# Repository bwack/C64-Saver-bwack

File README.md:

C64 Saver v1 and v2
- Overvoltage protection for the C64 and its power brick.

Designed by BWACK 2018
CERN OPEN HARDWARE LICENSE v1.2
http://www.ohwr.org/

The KiCad and other design files are available on GitHub:
https://github.com/bwack/

All text above must be included in any redistribution

# Warning: latest version of the savers are not tested.

# Bwack's C64 saver designs.

The C64 Saver 2 is an open-source project intended to make overvoltage protection available and easy to make for anyone interested in using the old Commodore power brick together with the C64. The power brick is 30-40 years old, and it is known for failure with overvoltage. This is caused sometimes because of broken solder joints on the regulator or the regulator itself failing.

## What has changed in v2 ?
- The design is modular.
- Spike protection. Handles hotswapping and switch bouncing better.
- It is much much easier and faster to make. Most people can make it!

## The base board (C64 Saver 2 SMD or Throughhole)
The base board is all you need for overvoltage protection. Through hole parts except for the mosfet, but it is large and easy to solder, no special tools needed other than your solder iron. The board shape fits the Hammond 1551g project case.
* Note: You need to bridge pin 4 and 5 in J2 and pin 4 and 5 in J4 if you are not using the base board in combination with the addon board or the relay board. The reason for this is that, with the addon board, we need to route the current through a sensing circuit. When the addon board is not used, we need to route it directly to the mosfet and terminals.

There is also a SMD version for those who like to reflow soldering.

## The addon board
The C64 saver addon board is a hat for the base board, and adds software control, instrumentation on both ac and dc side, and an optional 128x32 OLED display. The aim for this project is to make a tool for C64 repairers. The 9VAC and 5VDC are fully isolated. Software control and instrumentation is useful if you are repairing C64s. You can set the output to shut down in case of an overcurrent condition. If an overvoltage happens you can configure the saver to auto reset or keep the power from comming back on again. There are several reasons why you might want this. C64 PSUs that need service, the capacitors are dry and the 5VDC has an AC component on it. The saver would normally just go on and off at 100Hz. The software control can detect this. The other problem is if the computer has a faulty chip that cause massive current draw on the 5V. The fuse might not blow because it is not enough, then you can configure the saver cut if you desire. I'm not gonna lie. This is my pet project, and the cost has not been a topic on my mind.

The C64 Saver Addon Board 1.4:

Youtube video of me testing the addon board installed on the C64 Saver 2.

The relay and hold board is archived in the oldfiles folder.

## C64 Saver OCP

OCP, not robocop, but overcurrent protection. Is a new circuit that I'm working on. It has three LEDs and a button. The overvoltage protection circuit is the same as before. The overcurrent will light the yellow led and keep it lit and keep the output OFF after an overcurrent event.

## The old design
I have decided to release my older C64 Saver v1. The board that fits inside a connector. Time and skill is super high on this product so be warned ! (SMD 0603, solder blob connections, tight spaces and short circuit hazards).

## Gerbers
If you are looking for gerbers, click the releases tab. There you will find a zip file of gerber for each release.

# BOM
All bill of materials (BOM) are moved into the respective project folders. I have added digikey etc order no. in the parts in the schematics such that they will show up in the interactive boms.

Here are the interactive BOMs:

[ibom for C64 Saver Throughole 2.6](https://htmlpreview.github.io/?https://github.com/bwack/C64-Saver-bwack/blob/master/C64%20Saver%20Throughhole%202.6/bom/ibom.html)

[ibom for C64 Saver SMD 2.6](https://htmlpreview.github.io/?https://github.com/bwack/C64-Saver-bwack/blob/master/C64%20Saver%20SMD%202.6/bom/ibom.html)

[ibom for C64 Addon Board 1.4](https://htmlpreview.github.io/?https://github.com/bwack/C64-Saver-bwack/blob/master/addon%20board%201.4/bom/ibom.html)

[ibom for C64 Saver OCP 0.1](https://htmlpreview.github.io/?https://github.com/bwack/C64-Saver-bwack/blob/master/C64%20Saver%20OCP%200.1/bom/ibom.html)

# Changelog:

- C64 Saver 2.6 (THT+SMD) and Addon Board 1.4 (2023-04-02)
  - Replaced 7n2002 with BC547/BC847 to fix the tolerance issues.
  - Throughhole and SMD: same version numbers, same circuits, same reference numbers.
  - Red LED is switched by TL431 and Green by BC547/BC847.
  - Added LEDs to the Throughhole version. It was a challenge.
  - Fix: The Addon Board 1.3 had incorrect pinout for the 5V reg.
  - I never tested the Addon Board 1.3, but thanks to Retroisten who sent.
  me images and advicing me about he pinout, I'm very happy about it. He also
  showed me that it does work, with the regulator hacked in.  In this version 1.4
  it is working.

- C64 Saver 2.5 (SMD) (2020-09-13)
  - Added fault LED and power LED
  - 0805 SMD resistors
  - SOT23-5 TL431 and NMOS

- RelayHold 0.2 (2019-08-25)
  - Initial release
  - All through-hole parts.

- Addon Board 1.3 (2019-05-24)
  - Changed optocoupler footprint to more common SOIC-4_4.55x2.6mm_P1.27mm
  - Larger 5V regulator on 9vac side for less heat
  - replaced 100uF tantalum with 3x 47uF 1206 MLCC
  - kicad 5.1.0 project

- Addon Board 1.2 (2018-11-11)
  - Swapped HOLD_ with SENSE_VAC on the MCU. SENSE_VAC needs ADC.
  - Correct the mixed up SDA and SCL.
  - 5V supply to the 5V section is moved to VIN+ (before the shunt).
    To not pull power through the sensing resistor.
  - 4k7 I2C pullups.https://htmlpreview.github.io/?https://github.com/bwack/C64-Saver-bwack/blob/develop/C64%20Saver%20Throughhole%202.6/bom/ibom.html

- C64 Saver 2.4 (2018-09-23)
  - Support lower Vth on Q1. Resistor divider R7 and R8.
  - Remove C2 to make room for resistor divider.
  - Changed R5 to 3k3 to reduce BOM size.
  - New layout and routing.

- Addon Board 1.1 (2018-09-23)
  - ATtiny85 is a 8S2 package and two mm wider than SOIC8.
  - Read overvoltage signal on reset pin using ADC. Added voltage divider.
  - Replace MCP1700 with MCP1703. Supporting higher Vin_max

- C64 Saver 2.3 (2018-08-18)
  - Q1 2N7002 pin 1 and 2 rotated
  - Q2 Reversed drain and source
  - Increased pullup on Q1 drain.
  - Repurposed R5 as pullup for Q1 drain.
  - tested bodged v2.2 prototype, wohttps://htmlpreview.github.io/?https://github.com/bwack/C64-Saver-bwack/blob/develop/C64%20Saver%20Throughhole%202.6/bom/ibom.htmlrking!

- C64 Saver 2.2 (2018-08-16)
  - R1 was rotated.

- C64 Saver 2.1 & Addon 1.0 (2018-07-23)
  - 5x 9VAC pins. 9VAC1 current (4x) + 9VAC2.
  - Moved GND pin.
  - Changed board size to fit Hammond1551g
  - C64 Saver board:
    - Smaller throughole resistors
    - Moved C1 closer to input circuits.
  - Addon board:
    - VAC sense circuit with voltage divider.
    - 5V regulator on VCC pin. RAW pin disconnected.
    - Pullups on I2C busses.
    - SSOP-4 optocoupler packages
    - Another regulator on the 5V side to protect the iso1541 and ina219.

- C64 Saver 2.0beta & Addon 1.0beta (2018-07-02)
  - New design.
  - Protected sensitive parts.
  - baseboard: throughhole parts.
  - C64 saver 2 addon board.
  - problem: has conflicting pinouts.

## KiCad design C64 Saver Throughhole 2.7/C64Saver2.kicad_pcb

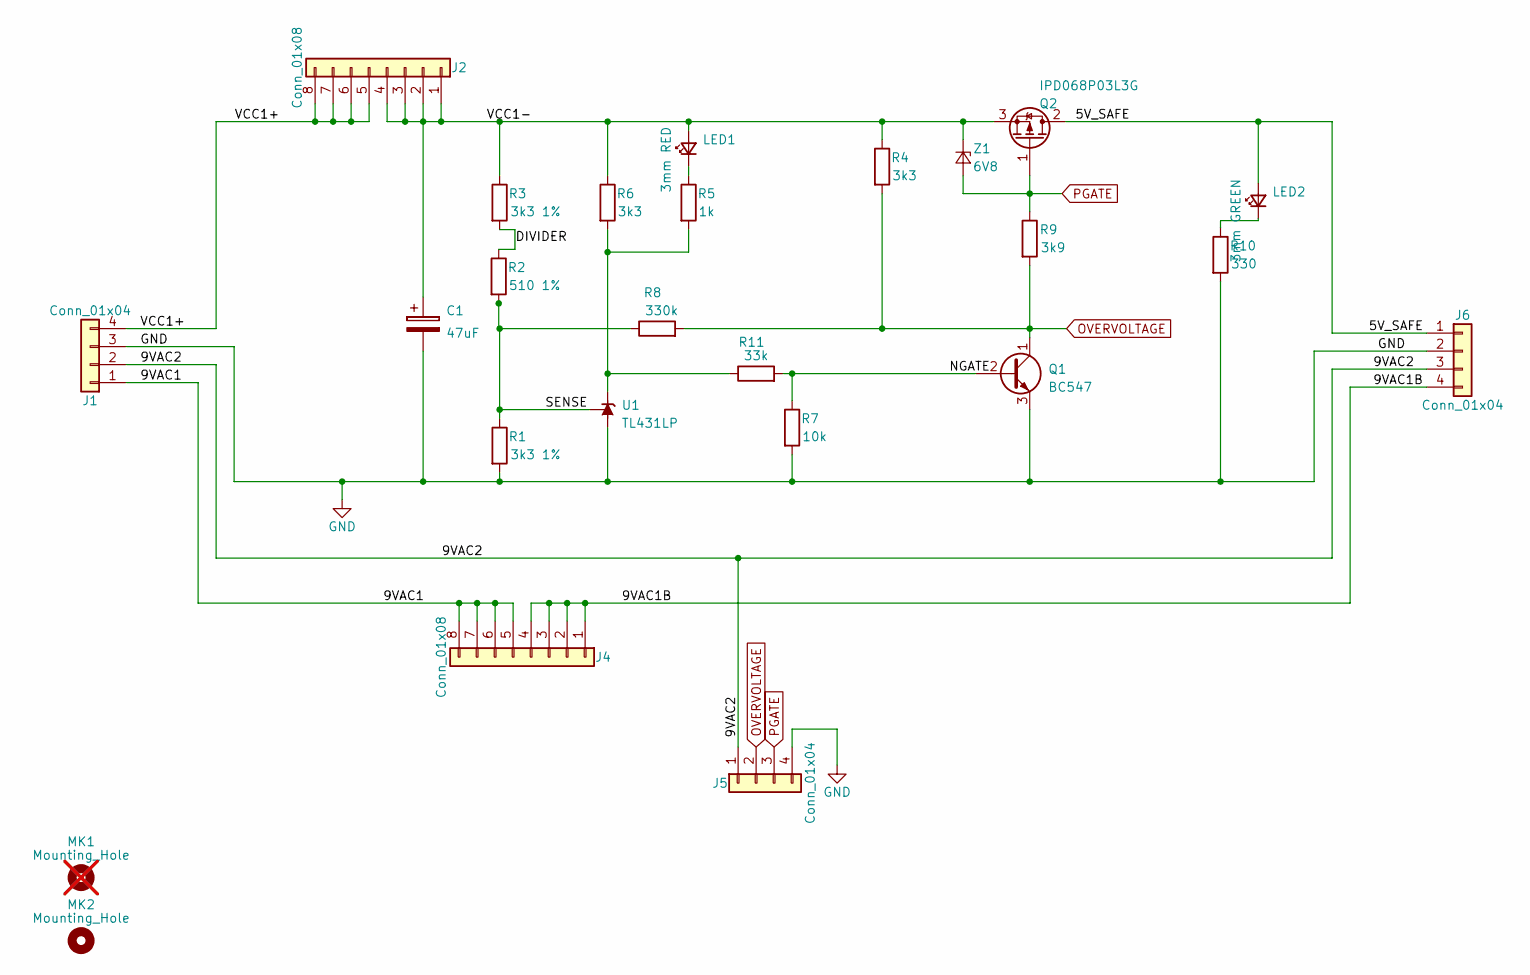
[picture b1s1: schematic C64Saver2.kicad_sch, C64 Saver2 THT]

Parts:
C1: 47uF; CP_Radial_D6.3mm_P2.50mm
J1, J6: Conn_01x04; TerminalBlock_bornier-4_P5.08mm; Mouser not used
J2, J4: Conn_01x08; Pin_Header_Straight_1x08_Pitch2.54mm
J5: Conn_01x04; Pin_Header_Straight_1x04_Pitch2.54mm
LED1: 3mm RED; LED_D3.0mm_Easy_1; Mouser WP710A10LSECK/J3
LED2: 3mm GREEN; LED_D3.0mm_Easy_2; Mouser WP710A10LZGCK
MK1: Mounting_Hole; MountingHole_2.5mm; not fitted
MK2: Mounting_Hole; MountingHole_2.5mm
Q1: BC547; TO-92_Inline_Wide
Q2: IPD068P03L3G; ATPAK-2
R1: 3k3 1%; R_Axial_DIN0204_L3.6mm_D1.6mm_P5.08mm_Horizontal; Mouser RN55D3301FB14
R2: 510 1%; R_Axial_DIN0204_L3.6mm_D1.6mm_P5.08mm_Horizontal
R3: 3k3 1%; R_Axial_DIN0204_L3.6mm_D1.6mm_P5.08mm_Horizontal
R4, R6: 3k3; R_Axial_DIN0204_L3.6mm_D1.6mm_P5.08mm_Horizontal; Mouser RN55D3301FB14
R5: 1k; R_Axial_DIN0204_L3.6mm_D1.6mm_P5.08mm_Horizontal
R7: 10k; R_Axial_DIN0204_L3.6mm_D1.6mm_P5.08mm_Horizontal
R8: 330k; R_Axial_DIN0204_L3.6mm_D1.6mm_P5.08mm_Horizontal
R9: 3k9; R_Axial_DIN0204_L3.6mm_D1.6mm_P5.08mm_Horizontal
R10: 330; R_Axial_DIN0204_L3.6mm_D1.6mm_P5.08mm_Horizontal
R11: 33k; R_Axial_DIN0207_L6.3mm_D2.5mm_P7.62mm_Horizontal
U1: TL431LP; TO-92_Inline_Wide
Z1: 6V8; D_DO-35_SOD27_P7.62mm_Horizontal

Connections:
/5V_SAFE: J6.1, LED2.2 (A), Q2.2 (D)
/9VAC1: J1.1, J4.5, J4.6, J4.7, J4.8
/9VAC1B: J4.1, J4.2, J4.3, J4.4, J6.4
/9VAC2: J1.2, J5.1, J6.3
/DIVIDER: R2.1, R3.2
/NGATE: Q1.2 (B), R7.1, R11.2
/SENSE: R1.1, R2.2, R8.1, U1.1 (REF)
/VCC1+: J1.4, J2.5, J2.6, J2.7, J2.8
/VCC1-: C1.1, J2.1, J2.2, J2.3, J2.4, LED1.2 (A), Q2.3 (S), R3.1, R4.1, R6.1, Z1.1 (K)
GND: C1.2, J1.3, J5.4, J6.2, Q1.3 (E), R1.2, R7.2, R10.2, U1.2 (A)
unnamed: LED1.1 (K), R5.1
unnamed: LED2.1 (K), R10.1
unnamed: R5.2, R6.2, R11.1, U1.3 (K)
OVERVOLTAGE: J5.2, Q1.1 (C), R4.2, R8.2, R9.2
PGATE: J5.3, Q2.1 (G), R9.1, Z1.2 (A)

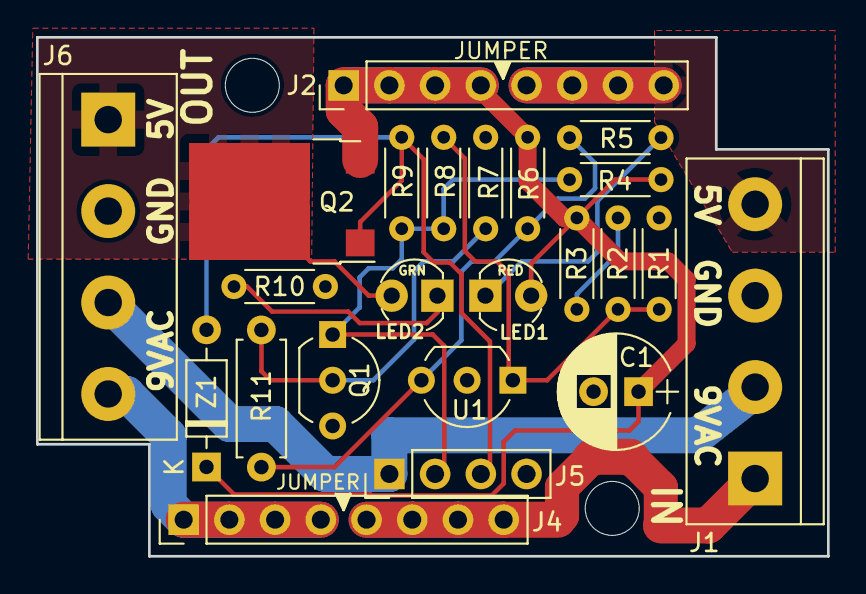
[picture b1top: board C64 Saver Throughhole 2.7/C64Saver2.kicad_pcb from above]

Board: 2 copper layers, 43.9 x 28.8 mm, 25 parts (0 on the bottom side), 15 nets.

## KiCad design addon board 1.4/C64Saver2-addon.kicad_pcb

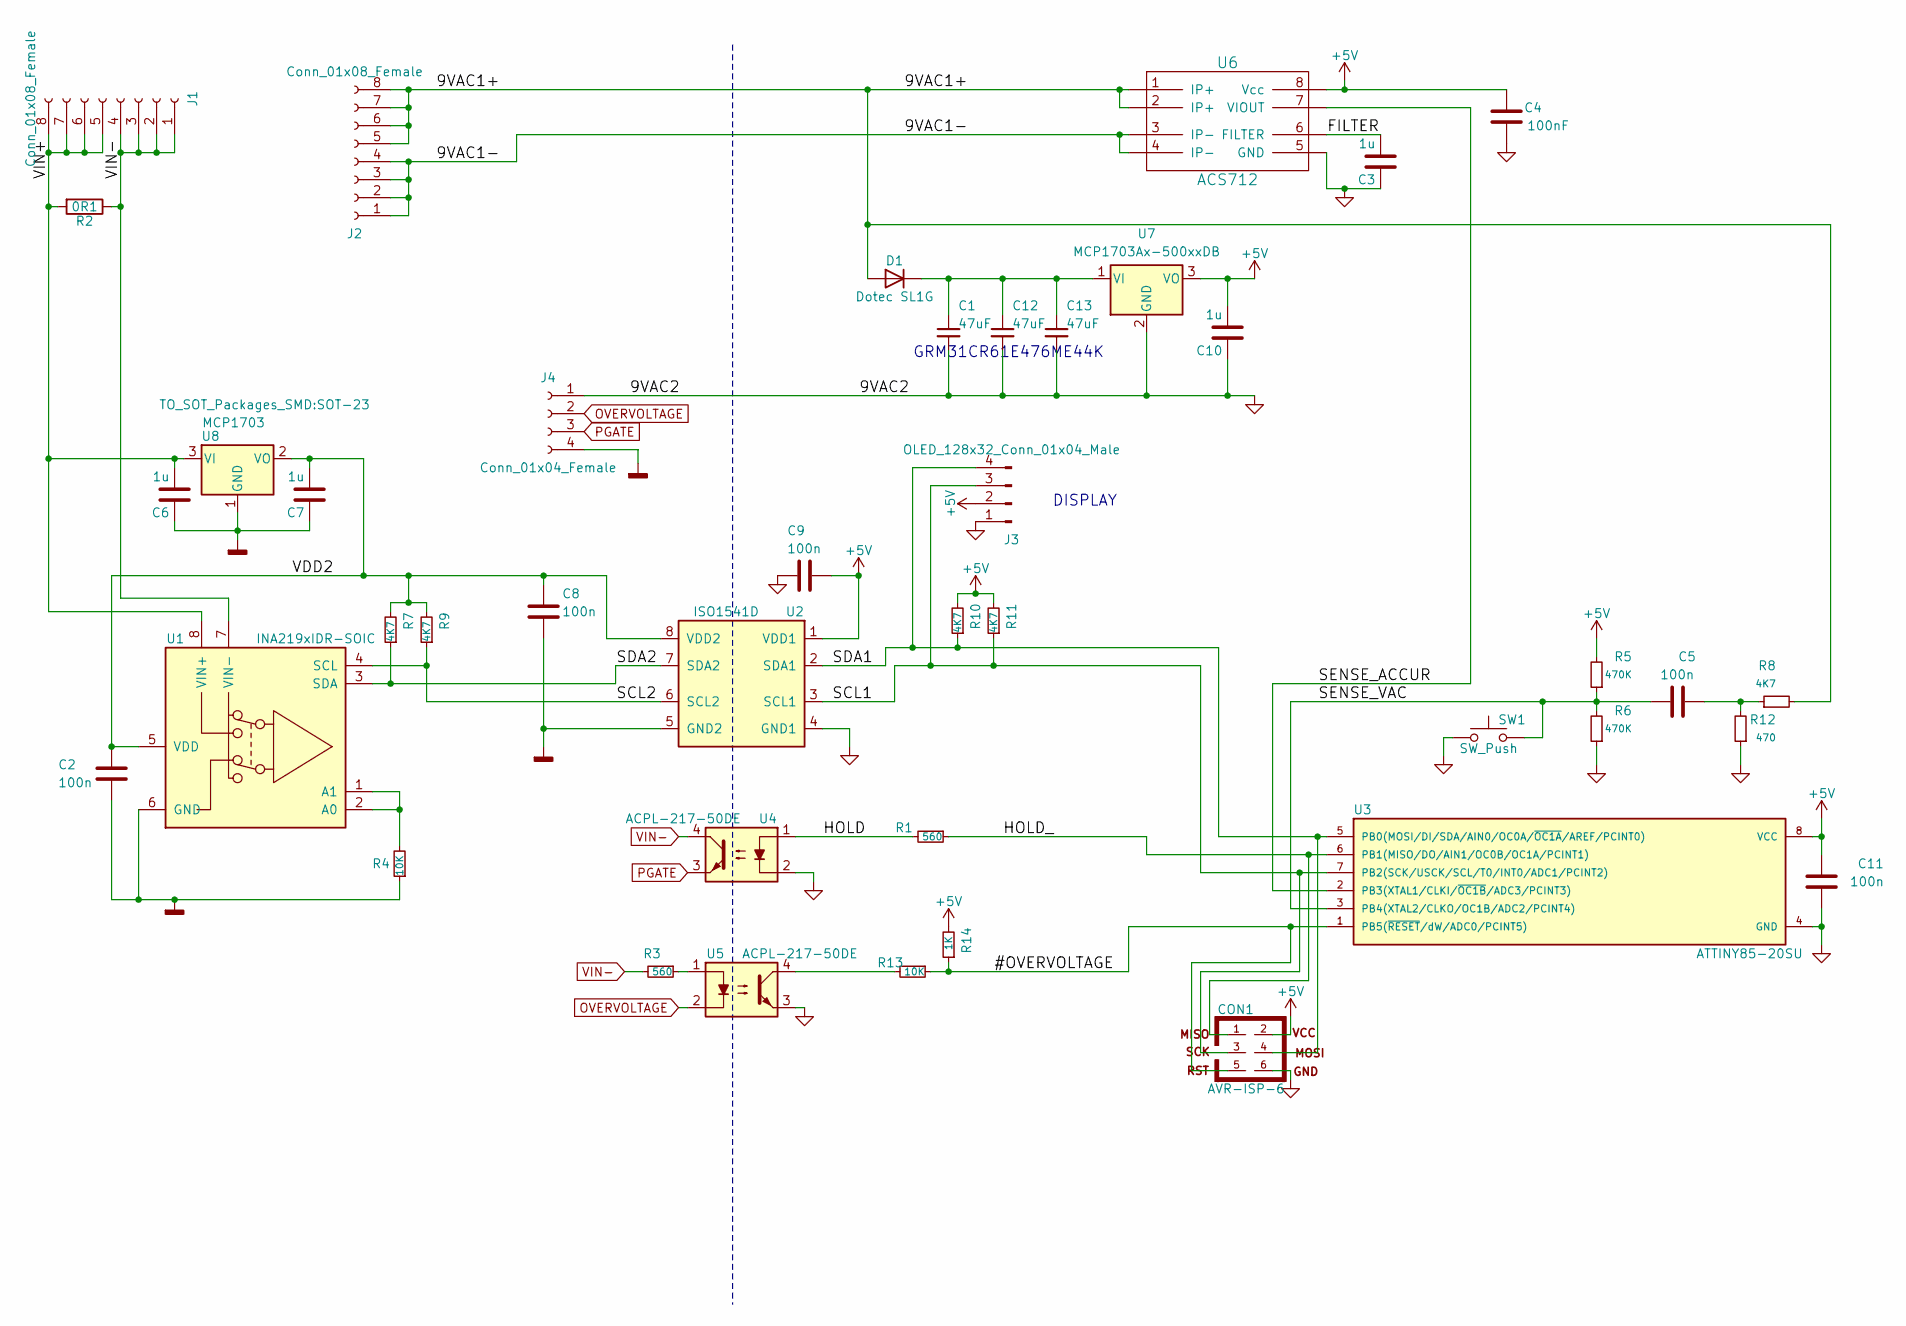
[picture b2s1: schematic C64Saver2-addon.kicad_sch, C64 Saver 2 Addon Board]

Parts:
C1, C12, C13: 47uF; C_1206_3216Metric
C2, C5, C8, C9, C11: 100n; C_0603_HandSoldering
C3, C6, C7, C10: 1u; C_0603_HandSoldering
C4: 100nF; C_0603_HandSoldering
CON1: AVR-ISP-6; Pin_Header_Straight_2x03_Pitch2.00mm
D1: Dotec SL1G; D_SOD-123
J1, J2: Conn_01x08_Female; Pin_Header_Straight_1x08_Pitch2.54mm
J3: OLED_128x32_Conn_01x04_Male; Pin_Header_Straight_1x04_Pitch2.54mm
J4: Conn_01x04_Female; Pin_Header_Straight_1x04_Pitch2.54mm
R1, R3: 560; R_0603_HandSoldering
R2: 0R1; R_2512_HandSoldering
R4, R13: 10K; R_0603_HandSoldering
R5: 470K; R_0603_HandSoldering
R6: 470K; R_0603_1608Metric_Pad1.05x0.95mm_HandSolder
R7, R8, R9, R10, R11: 4K7; R_0603_HandSoldering
R12: 470; R_0603_HandSoldering
R14: 1K; R_0603_HandSoldering
SW1: SW_Push; SW_PUSH_6mm_h13mm
U1: INA219xIDR-SOIC; SOIC-8_3.9x4.9mm_P1.27mm
U2: ISO1541D; SOIC-8_3.9x4.9mm_P1.27mm
U3: ATTINY85-20SU; SOIJ-8_5.3x5.3mm_P1.27mm
U4, U5: ACPL-217-50DE; SOIC-4_4.55x2.6mm_P1.27mm
U6: ACS712; SOIC-8_3.9x4.9mm_P1.27mm
U7: MCP1703Ax-500xxDB; SOT-223-3_TabPin2
U8: MCP1703; SOT-23

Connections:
+5V: C4.2, C9.1, C10.2, C11.2, CON1.2, J3.2, R5.2, R10.2, R11.2, R14.2, U2.1 (VDD1), U3.8 (VCC), U6.8 (Vcc), U7.3 (VO)
/9VAC1+: D1.2 (A), J2.5, J2.6, J2.7, J2.8, R8.2, U6.1 (IP+), U6.2 (IP+)
/9VAC1-: J2.1, J2.2, J2.3, J2.4, U6.3 (IP-), U6.4 (IP-)
/#OVERVOLTAGE: CON1.5, R13.1, R14.1, U3.1 (PB5(~RESET/dW/ADC0/PCINT5))
/FILTER: C3.2, U6.6 (FILTER)
/HOLD: R1.2, U4.1
/HOLD_: CON1.1, R1.1, U3.6 (PB1(MISO/DO/AIN1/OC0B/OC1A/PCINT1))
/SCL1: CON1.3, J3.3, R11.1, U2.3 (SCL1), U3.7 (PB2(SCK/USCK/SCL/T0/INT0/ADC1/PCINT2))
/SCL2: R9.1, U1.4 (SCL), U2.6 (SCL2)
/SDA1: CON1.4, J3.4, R10.1, U2.2 (SDA1), U3.5 (PB0(MOSI/DI/SDA/AIN0/OC0A/~OC1A/AREF/PC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)
/SDA2: R7.1, U1.3 (SDA), U2.7 (SDA2)
/SENSE_ACCUR: U3.2 (PB3(XTAL1/CLKI/~OC1B/ADC3/PCINT3)), U6.7 (VIOUT)
/SENSE_VAC: C5.2, R5.1, R6.2, SW1.2, U3.3 (PB4(XTAL2/CLKO/OC1B/ADC2/PCINT4))
/VDD2: C2.1, C7.2, C8.1, R7.2, R9.2, U1.5 (VDD), U2.8 (VDD2), U8.2 (VO)
/VIN+: C6.2, J1.5, J1.6, J1.7, J1.8, R2.2, U1.8 (VIN+), U8.3 (VI)
GND: C1.2, C3.1, C4.1, C9.2, C10.1, C11.1, C12.2, C13.2, CON1.6, J3.1, J4.1, R6.1, R12.1, SW1.1, U2.4 (GND1), U3.4 (GND), U4.2, U5.3, U6.5 (GND), U7.2 (GND)
GNDD: C2.2, C6.1, C7.1, C8.2, J4.4, R4.1, U1.6 (GND), U2.5 (GND2), U8.1 (GND)
unnamed: C5.1, R8.1, R12.2
unnamed: C1.1, C12.1, C13.1, D1.1 (K), U7.1 (VI)
unnamed: R3.1, U5.1
unnamed: R13.2, U5.4
unnamed: R4.2, U1.1 (A1), U1.2 (A0)
OVERVOLTAGE: J4.2, U5.2
PGATE: J4.3, U4.3
VIN-: J1.1, J1.2, J1.3, J1.4, R2.1, R3.2, U1.7 (VIN-), U4.4

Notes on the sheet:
DISPLAY
GRM31CR61E476ME44K

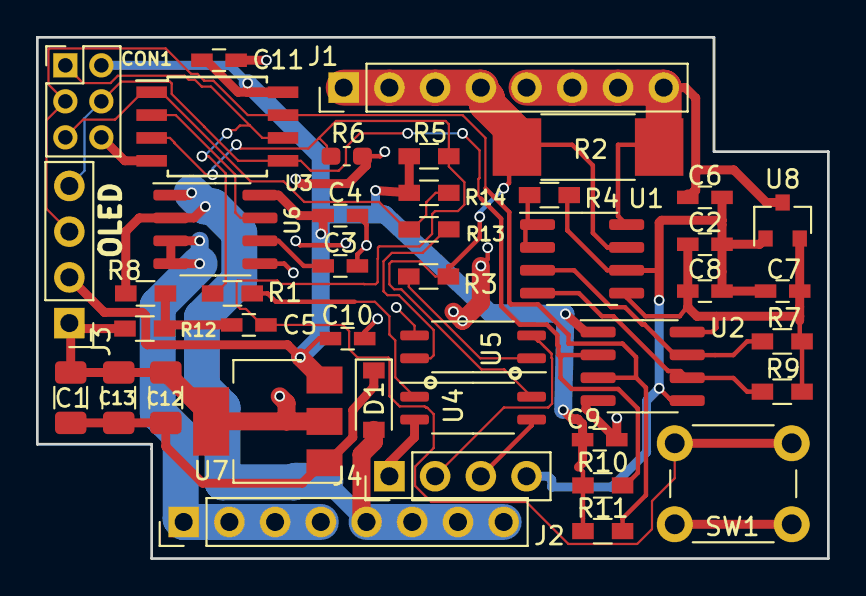
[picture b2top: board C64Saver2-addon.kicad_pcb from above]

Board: 2 copper layers, 43.9 x 29.0 mm, 42 parts (0 on the bottom side), 25 nets.

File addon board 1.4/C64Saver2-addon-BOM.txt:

BOM for the C64 Saver 2 addon board v1.3
======================================== 

To be updated !

pcs  ref                 value     description                  elfa#       RS#
---------------------------------------------------------------------------------
1    C1
6    C2,C4,C5,   100nF     SMD Capacitor 0603                   301-11-165
     C8,C9,C11
4    C3,C6,C7,   1u        SMD Capacitor 0603                   300-87-136
     C10
1    D1          SL1G      SMD SOD-123 - Diotec SL1G            170-02-190
2    J1,J2       1x8       Conn Male Straight P2.54mm           300-93-649
1    J3          1x4       Conn Female Straight P2.54mm + OLED  300-93-664
1    J4          1x4       Conn Male Straight P2.54mm           300-93-645
4    R7,R8,R9,   4k7
     R10,R11
6    R1,R3       560R      Resistor SMD 0603                    300-37-977
1    R2          0R1       Shunt Resistor SMD 2512              160-30-965
2    R4,R13      10K       Resistor SMD 0603                    300-47-287
2    R5,R6       470k      Resistor SMD 0603                    300-37-953
1    R12         470R      Resistor SMD 0603                    300-37-950
1    R14         1K        Resistor SMD 0603                    160-15-663
1    SW1         SW_Push   SW_PUSH 6mm h13mm                    300-90-650
1    U1          INA219    SMD SOIC-8                                       817-6580
1    U2          ISO1541D  Optoisolated I2C tranciever SOIC-8   300-22-572  825-3075
1    U3          ATTINY85  MCU Atmel ATTINY85-SU,               173-21-927
                           SOIJ-8_5.3x5.3mm_Pitch1.27mm
2    U4,U5       ACPL-217-50DE
1    U6          ACS712    Hal-effect ADC I2C SMD SOIC-8                    680-7131
1    U8          MCP1703T  LDO 5V reg 16Vin_max                             775-7450
                           MCP1703T-5002E/CB SOT-23A-3

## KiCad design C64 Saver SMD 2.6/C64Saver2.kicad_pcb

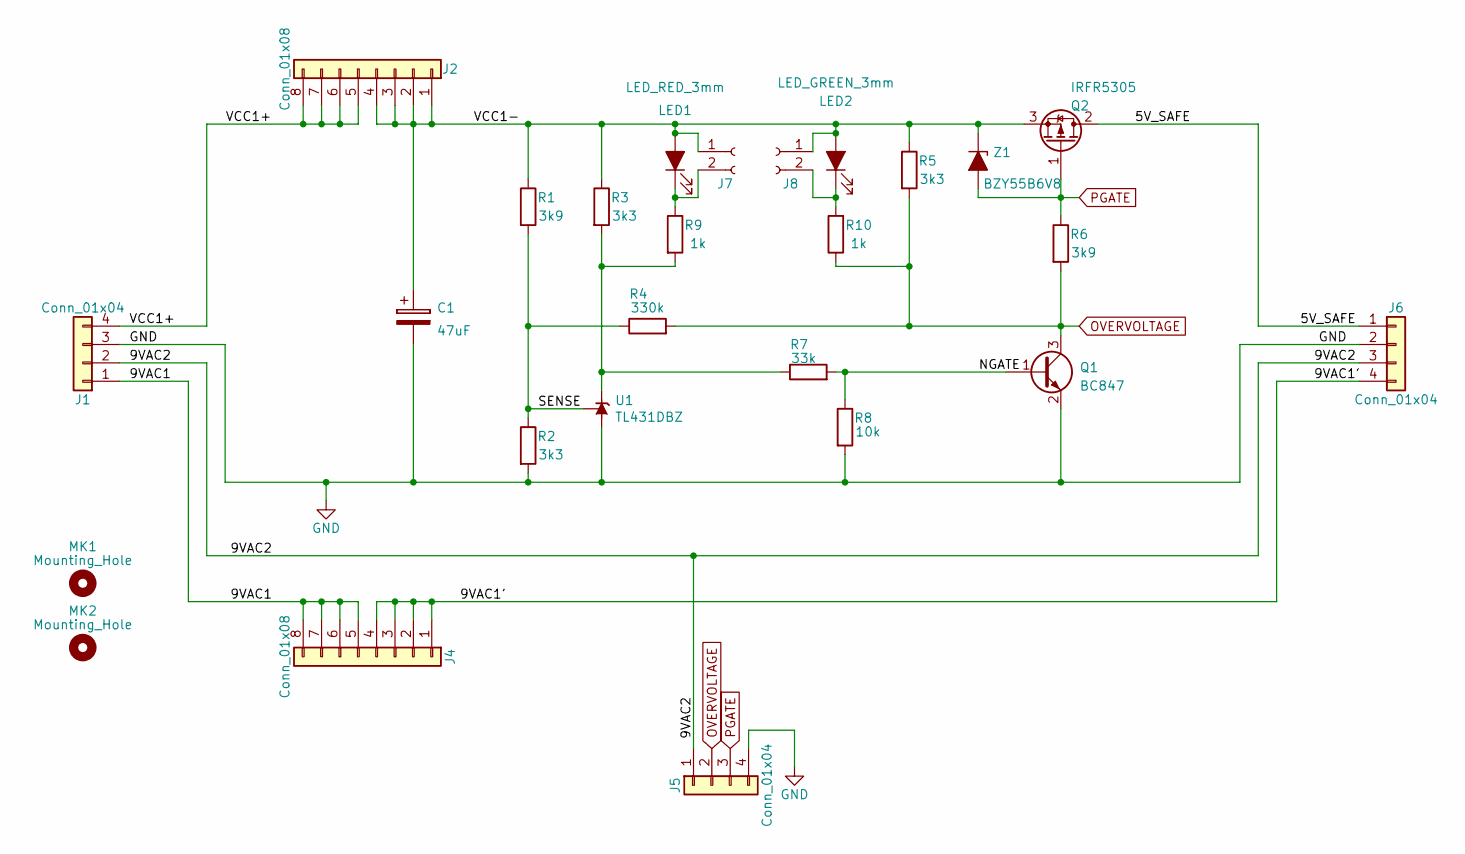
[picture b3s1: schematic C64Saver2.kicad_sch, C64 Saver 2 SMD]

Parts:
C1: 47uF; CP_Elec_6.3x5.4; Digi-Key 493-3935-1-ND
J1, J6: Conn_01x04; TerminalBlock_bornier-4_P5.08mm
J2, J4: Conn_01x08; Pin_Header_Straight_1x08_Pitch2.54mm
J5: Conn_01x04; Pin_Header_Straight_1x04_Pitch2.54mm
J7, J8: Conn_01x02_Socket; PinHeader_1x02_P2.54mm_Vertical
LED1: LED_RED_3mm; LED_0805_2012Metric_Pad1.15x1.40mm_HandSolder; Digi-Key 160-1956-ND
LED2: LED_GREEN_3mm; LED_0805_2012Metric_Pad1.15x1.40mm_HandSolder; Digi-Key 160-1142-ND
MK1, MK2: Mounting_Hole; MountingHole_2.5mm
Q1: BC847; SOT-23; Digi-Key 1727-2921-1-ND
Q2: IRFR5305; ATPAK-2; Digi-Key IRFR5305TRLPBFCT-ND
R1, R6: 3k9; R_0805_2012Metric_Pad1.20x1.40mm_HandSolder; Digi-Key P3.90KCCT-ND
R2, R3, R5: 3k3; R_0805_2012Metric_Pad1.20x1.40mm_HandSolder; Digi-Key P3.30KCCT-ND
R4: 330k; R_0805_2012Metric_Pad1.20x1.40mm_HandSolder; Digi-Key P330KCCT-ND
R7: 33k; R_0805_2012Metric_Pad1.20x1.40mm_HandSolder; Digi-Key P33.0KCCT-ND
R8: 10k; R_0805_2012Metric_Pad1.20x1.40mm_HandSolder; Digi-Key P10.0KCCT-ND
R9, R10: 1k; R_0805_2012Metric_Pad1.20x1.40mm_HandSolder; Digi-Key P1.00KCCT-ND
U1: TL431DBZ; SOT-23; Digi-Key 296-26721-1-ND
Z1: BZY55B6V8; D_0805_2012Metric_Pad1.15x1.40mm_HandSolder; Digi-Key 1727-3668-1-ND

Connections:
/5V_SAFE: J6.1, Q2.2 (D)
/9VAC1: J1.1, J4.5, J4.6, J4.7, J4.8
/9VAC1': J4.1, J4.2, J4.3, J4.4, J6.4
/9VAC2: J1.2, J5.1, J6.3
/NGATE: Q1.1 (B), R7.2, R8.1
/SENSE: R1.2, R2.1, R4.1, U1.2 (REF)
/VCC1+: J1.4, J2.5, J2.6, J2.7, J2.8
/VCC1-: C1.1, J2.1, J2.2, J2.3, J2.4, J7.1, J8.1, LED1.2 (A), LED2.2 (A), Q2.3 (S), R1.1, R3.1, R5.1, Z1.1 (K)
GND: C1.2, J1.3, J5.4, J6.2, Q1.2 (E), R2.2, R8.2, U1.3 (A)
unnamed: J7.2, LED1.1 (K), R9.1
unnamed: J8.2, LED2.1 (K), R10.2
unnamed: R3.2, R7.1, R9.2, U1.1 (K)
OVERVOLTAGE: J5.2, Q1.3 (C), R4.2, R5.2, R6.2, R10.1
PGATE: J5.3, Q2.1 (G), R6.1, Z1.2 (A)

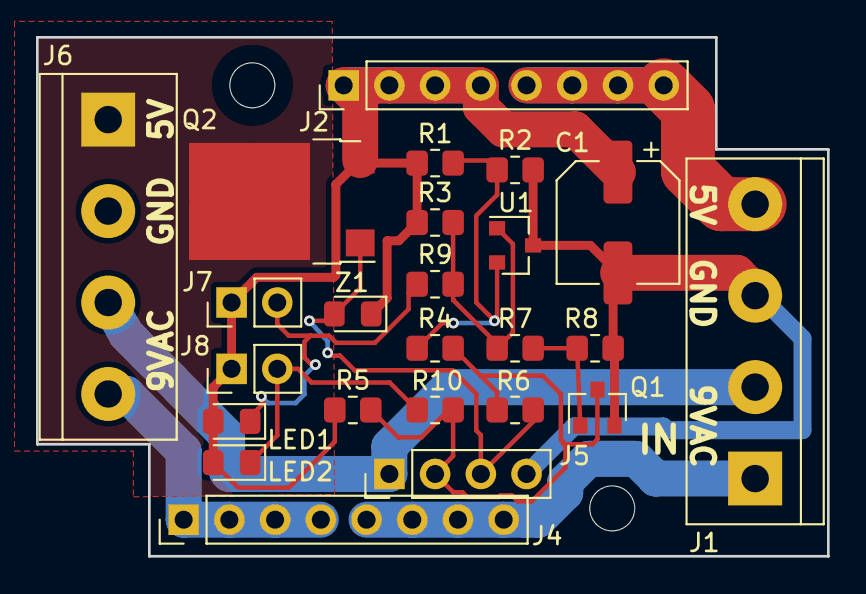
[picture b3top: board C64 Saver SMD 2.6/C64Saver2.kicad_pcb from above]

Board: 2 copper layers, 43.9 x 28.8 mm, 26 parts (0 on the bottom side), 14 nets.

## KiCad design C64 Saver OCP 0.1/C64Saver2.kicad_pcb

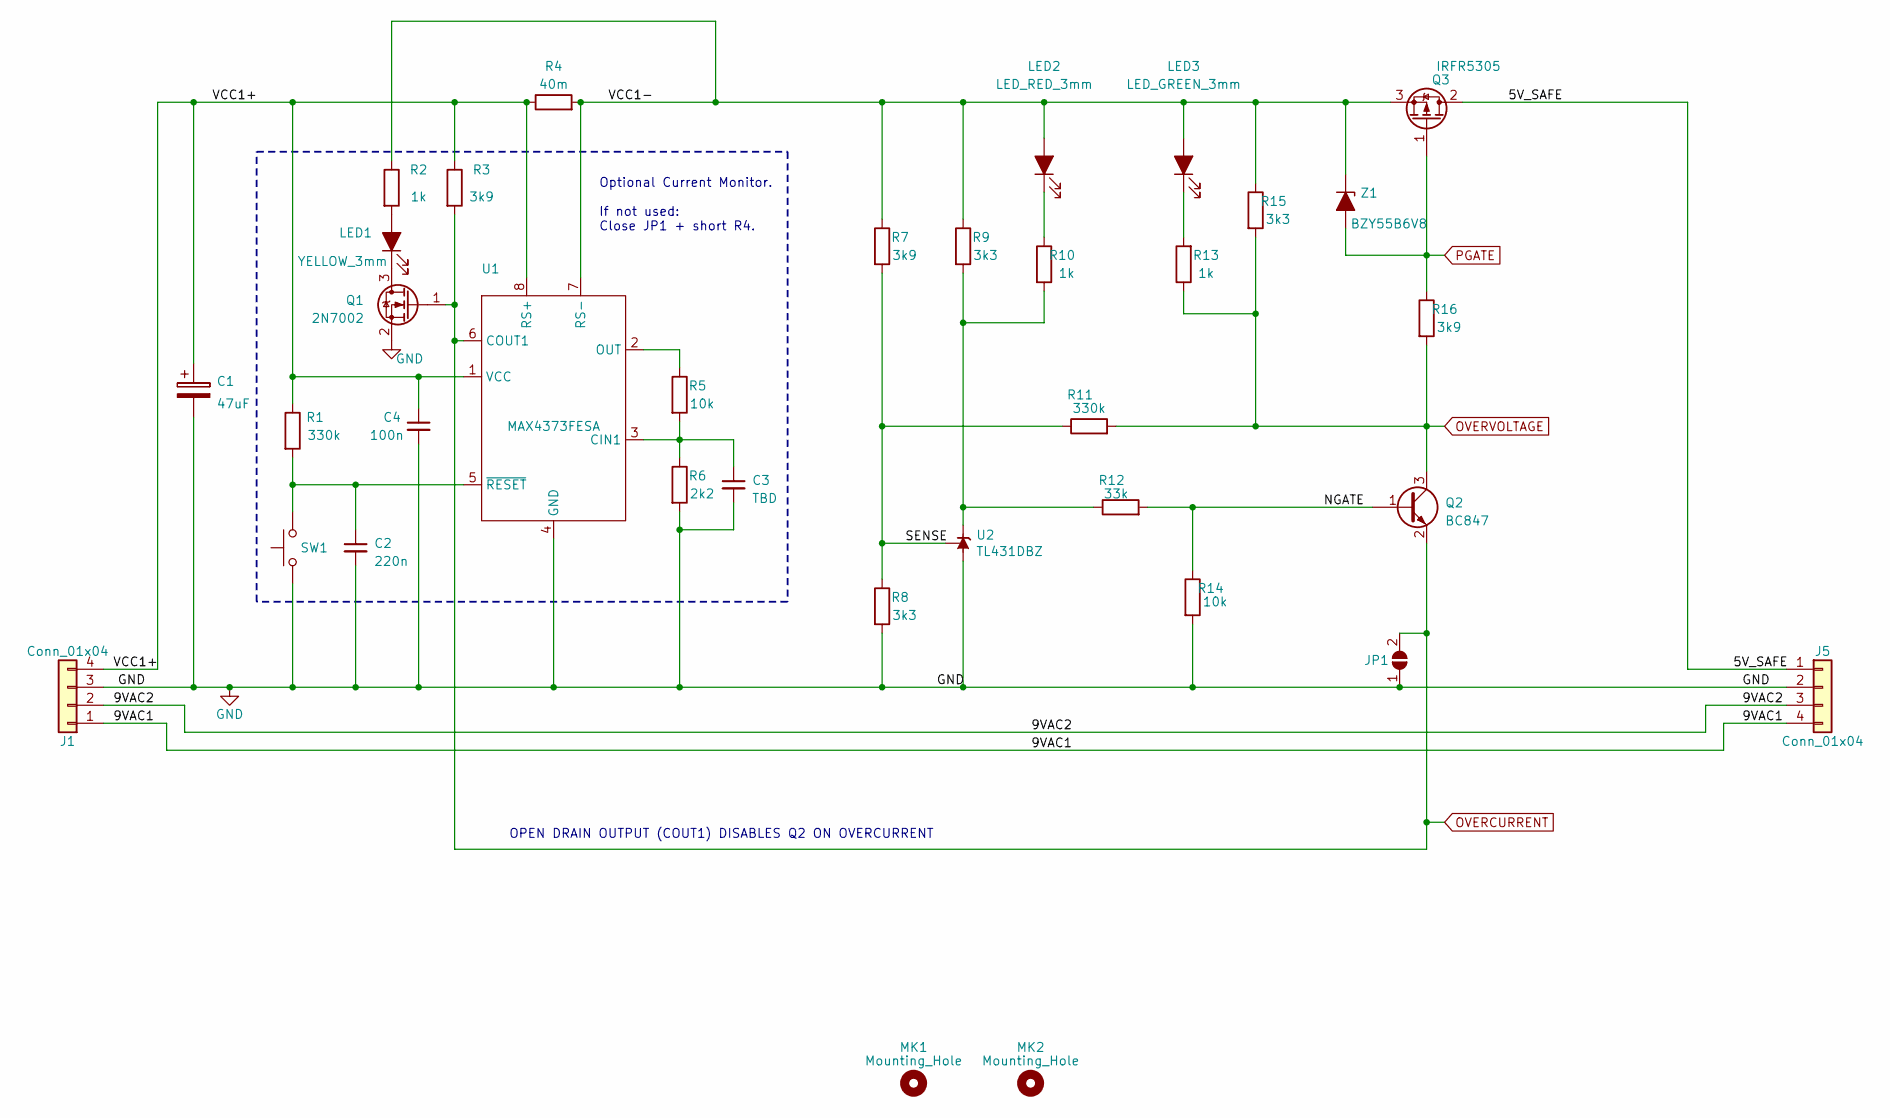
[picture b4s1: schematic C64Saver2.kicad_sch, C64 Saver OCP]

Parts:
C1: 47uF; CP_Elec_6.3x5.4; Digi-Key 493-3935-1-ND
C2: 220n; C_0603_1608Metric; Digi-Key 1276-1986-1-ND
C3: TBD; C_0603_1608Metric
C4: 100n; C_0603_1608Metric; Digi-Key 1276-1986-1-ND
J1, J5: Conn_01x04; TerminalBlock_bornier-4_P5.08mm; Digi-Key Not used
JP1: SolderJumper_2_Open; SolderJumper-2_P1.3mm_Open_RoundedPad1.0x1.5mm
LED1: YELLOW_3mm; LED_D3.0mm; Digi-Key 160-1968-ND
LED2: LED_RED_3mm; LED_D3.0mm; Digi-Key 160-1956-ND
LED3: LED_GREEN_3mm; LED_D3.0mm; Digi-Key 160-1142-ND
MK1, MK2: Mounting_Hole; MountingHole_2.5mm
Q1: 2N7002; SOT-23; Digi-Key 1727-8643-1-ND
Q2: BC847; SOT-23; Digi-Key 1727-2921-1-ND
Q3: IRFR5305; ATPAK-2; Digi-Key IRFR5305TRLPBFCT-ND
R1, R11: 330k; R_0603_1608Metric; Digi-Key P330KGCT-ND
R2, R10, R13: 1k; R_0603_1608Metric; Digi-Key P1.00KHCT-ND
R3, R7, R16: 3k9; R_0603_1608Metric; Digi-Key P3.9KGCT-ND
R4: 40m; R_2512_6332Metric; Digi-Key 1712-TLRP3A30WR040FTECT-ND
R5, R14: 10k; R_0603_1608Metric; Digi-Key P10.0KHCT-ND
R6: 2k2; R_0603_1608Metric; Digi-Key P2.20KHCT-ND
R8, R9, R15: 3k3; R_0603_1608Metric; Digi-Key P3.3KGCT-ND
R12: 33k; R_0603_1608Metric; Digi-Key P33KGCT-ND
SW1: SW_Push; SW_PUSH_6mm
U1: MAX4373FESA; SOIC-8_3.9x4.9mm_P1.27mm; Digi-Key MAX4373FESA+-ND
U2: TL431DBZ; SOT-23; Digi-Key 296-26721-1-ND
Z1: BZY55B6V8; D_0805_2012Metric_Pad1.15x1.40mm_HandSolder; Digi-Key 1727-3668-1-ND

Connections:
/5V_SAFE: J5.1, Q3.2 (D)
/9VAC1: J1.1, J5.4
/9VAC2: J1.2, J5.3
/NGATE: Q2.1 (B), R12.2, R14.1
/SENSE: R7.2, R8.1, R11.1, U2.2 (REF)
/VCC1+: C1.1, C4.1, J1.4, R1.1, R3.1, R4.1, U1.1 (VCC), U1.8 (RS+)
/VCC1-: LED2.2 (A), LED3.2 (A), Q3.3 (S), R2.1, R4.2, R7.1, R9.1, R15.1, U1.7 (RS-), Z1.1 (K)
GND: C1.2, C2.2, C3.2, C4.2, J1.3, J5.2, JP1.1 (A), Q1.2 (S), R6.2, R8.2, R14.2, SW1.2, U1.4 (GND), U2.3 (A)
unnamed: LED1.2 (A), R2.2
unnamed: LED1.1 (K), Q1.3 (D)
unnamed: LED2.1 (K), R10.1
unnamed: LED3.1 (K), R13.2
unnamed: C3.1, R5.2, R6.1, U1.3 (CIN1)
unnamed: R5.1, U1.2 (OUT)
unnamed: C2.1, R1.2, SW1.1, U1.5 (~RESET)
unnamed: R9.2, R10.2, R12.1, U2.1 (K)
OVERCURRENT: JP1.2 (B), Q1.1 (G), Q2.2 (E), R3.2, U1.6 (COUT1)
OVERVOLTAGE: Q2.3 (C), R11.2, R13.1, R15.2, R16.2
PGATE: Q3.1 (G), R16.1, Z1.2 (A)

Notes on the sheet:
OPEN DRAIN OUTPUT (COUT1) DISABLES Q2 ON OVERCURRENT
Optional Current Monitor. If not used: Close JP1 + short R4.

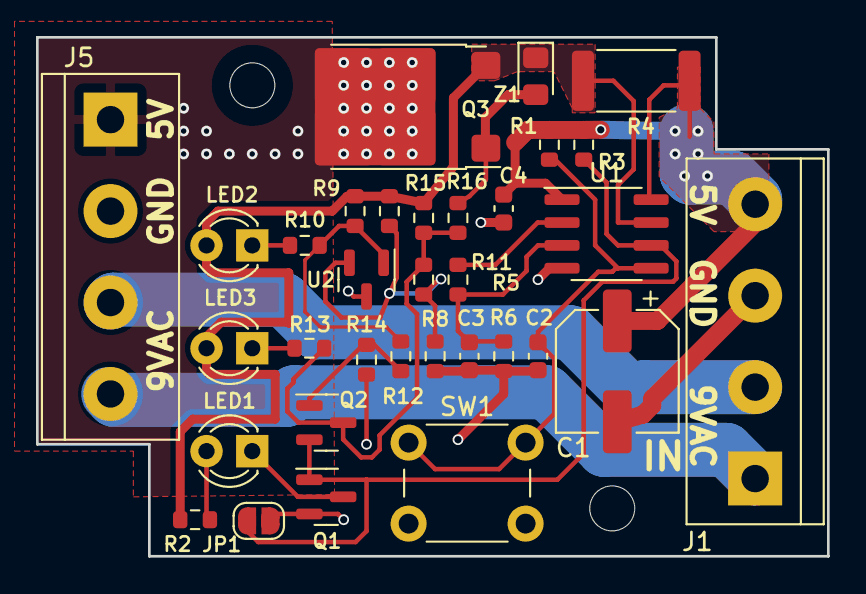
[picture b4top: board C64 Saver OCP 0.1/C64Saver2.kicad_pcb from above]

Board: 2 copper layers, 43.9 x 28.8 mm, 35 parts (0 on the bottom side), 19 nets.

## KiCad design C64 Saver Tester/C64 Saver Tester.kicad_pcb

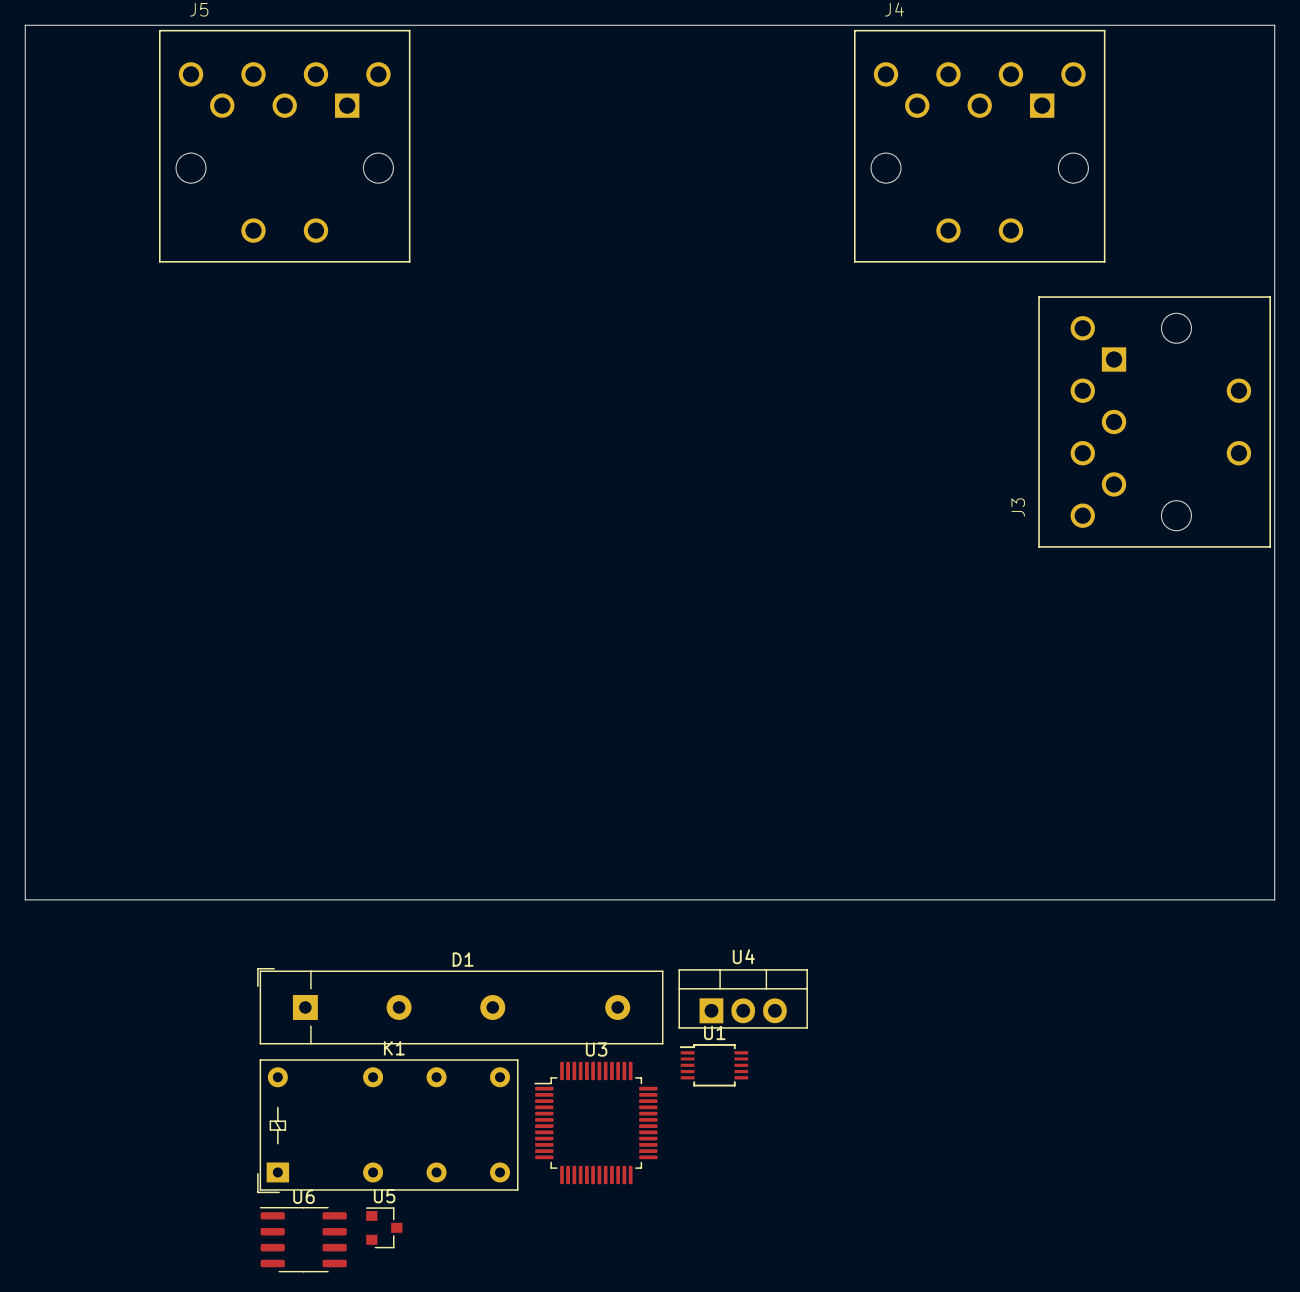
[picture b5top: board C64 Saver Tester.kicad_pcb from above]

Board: 2 copper layers, 100.0 x 70.0 mm, 10 parts (0 on the bottom side), 10 nets, no tracks yet.

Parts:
D1: 121; Diode_Bridge_32.0x5.6x17.0mm_P10.0mm_P7.5mm
J3, J4, J5: DIN-7; CUI_SDS-70J
K1: FINDER-30.22; Relay_DPDT_Finder_30.22
U1: ADS1015IDGS; TSSOP-10_3x3mm_P0.5mm
U3: STM32F103C8Tx; LQFP-48_7x7mm_P0.5mm
U4: LM337_TO220; TO-220-3_Vertical
U5: MCP1700-3302E_SOT23; SOT-23
U6: INA219AxD; SOIC-8_3.9x4.9mm_P1.27mm

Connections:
+3V3: U3.9, U3.24, U3.36, U3.48, U5.2
GND: D1.1, J3.1, J3.2, J3.3, U3.8, U3.23, U3.35, U3.47, U5.1
unnamed: D1.4, U5.3
unnamed: D1.2, J3.7
unnamed: D1.3, J3.6
unnamed: J3.4, J3.5
unnamed: J4.1, J4.2, J4.3
unnamed: J4.4, J4.5
unnamed: J5.1, J5.2, J5.3
unnamed: J5.4, J5.5

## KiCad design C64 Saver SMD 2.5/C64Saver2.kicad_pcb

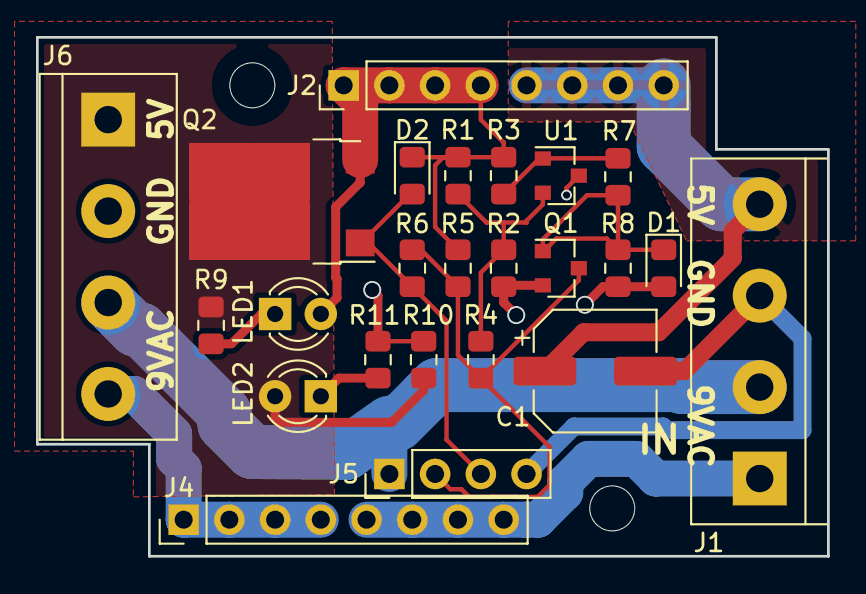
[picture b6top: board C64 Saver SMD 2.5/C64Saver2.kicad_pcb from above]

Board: 2 copper layers, 43.9 x 28.8 mm, 26 parts (0 on the bottom side), 14 nets.

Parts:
C1: 47uF; CP_Elec_6.3x5.4
D1, D2: BZY55B6V8; D_0805_2012Metric_Pad1.15x1.40mm_HandSolder
J1, J6: Conn_01x04; TerminalBlock_bornier-4_P5.08mm
J2, J4: Conn_01x08; Pin_Header_Straight_1x08_Pitch2.54mm
J5: Conn_01x04; Pin_Header_Straight_1x04_Pitch2.54mm
LED1: LED_RED_3mm; LED_D3.0mm
LED2: LED_GREEN_3mm; LED_D3.0mm
MK1, MK2: Mounting_Hole; MountingHole_2.5mm
Q1: 2N7002; SOT-23
Q2: IRFR5305; ATPAK-2
R1, R6: 3k9; R_0805_2012Metric_Pad1.15x1.40mm_HandSolder
R2, R3, R5, R9, R10, R11: 3k3; R_0805_2012Metric_Pad1.15x1.40mm_HandSolder
R4: 330k; R_0805_2012Metric_Pad1.15x1.40mm_HandSolder
R7: 33k; R_0805_2012Metric_Pad1.15x1.40mm_HandSolder
R8: 82k; R_0805_2012Metric_Pad1.15x1.40mm_HandSolder
U1: TL431DBZ; SOT-23

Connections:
/5V_SAFE: J6.1, LED2.2, Q2.2, R9.1, R10.2
/9VAC1: J1.1, J4.5, J4.6, J4.7, J4.8
/9VAC1': J4.1, J4.2, J4.3, J4.4, J6.4
/9VAC2: J1.2, J5.1, J6.3
/NGATE: D1.1, Q1.1, R7.2, R8.1
/SENSE: R1.2, R2.1, R4.1, U1.2
/VCC1+: C1.1, J1.4, J2.5, J2.6, J2.7, J2.8
/VCC1-: D2.1, J2.1, J2.2, J2.3, J2.4, LED1.2, Q2.3, R1.1, R3.1, R5.1
GND: C1.2, D1.2, J1.3, J5.4, J6.2, Q1.2, R2.2, R8.2, R10.1, R11.1, U1.3
unnamed: LED1.1, R9.2
unnamed: LED2.1, R11.2
unnamed: R3.2, R7.1, U1.1
OVERVOLTAGE: J5.2, Q1.3, R4.2, R5.2, R6.2
PGATE: D2.2, J5.3, Q2.1, R6.1
